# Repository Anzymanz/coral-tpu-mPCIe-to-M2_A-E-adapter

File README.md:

An M.2 A+E to mPCIe adapter for coral TPU

The capacitors most likely do not need to be populated

mPCIe Connector: [TE Connectivity 1775862-2](https://www.digikey.co.uk/en/products/detail/te-connectivity-amp-connectors/1775862-2/5430585)  
Standoffs: [Würth Elektronik 9774027151R](https://www.digikey.co.uk/en/products/detail/w%C3%BCrth-elektronik/9774027151R/5320625)  
  
**Make sure to disable ASPM to prevent the coral from sleeping and not being able to wake**  
Edit `/etc/default/grub`  
Example:  
`GRUB_CMDLINE_LINUX_DEFAULT="quiet intel_iommu=on pcie_aspm=off`

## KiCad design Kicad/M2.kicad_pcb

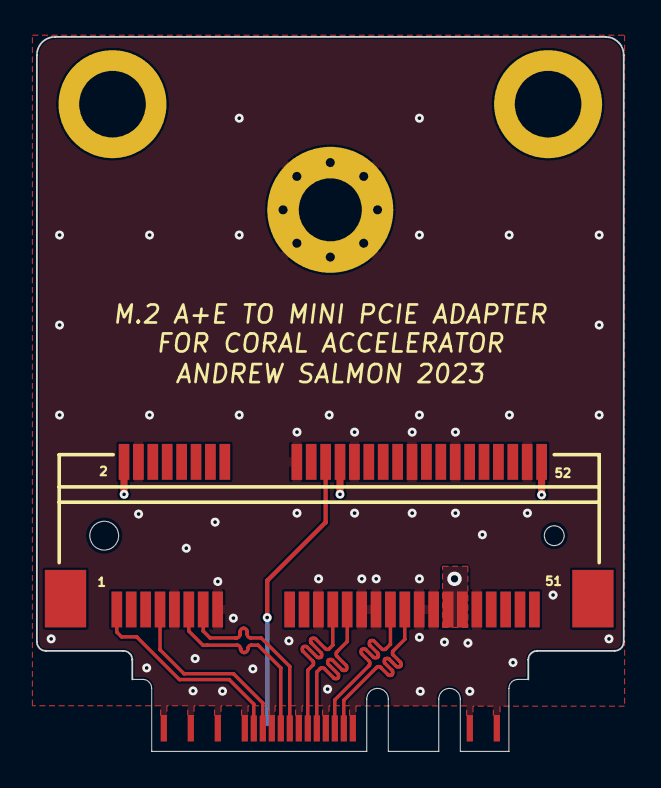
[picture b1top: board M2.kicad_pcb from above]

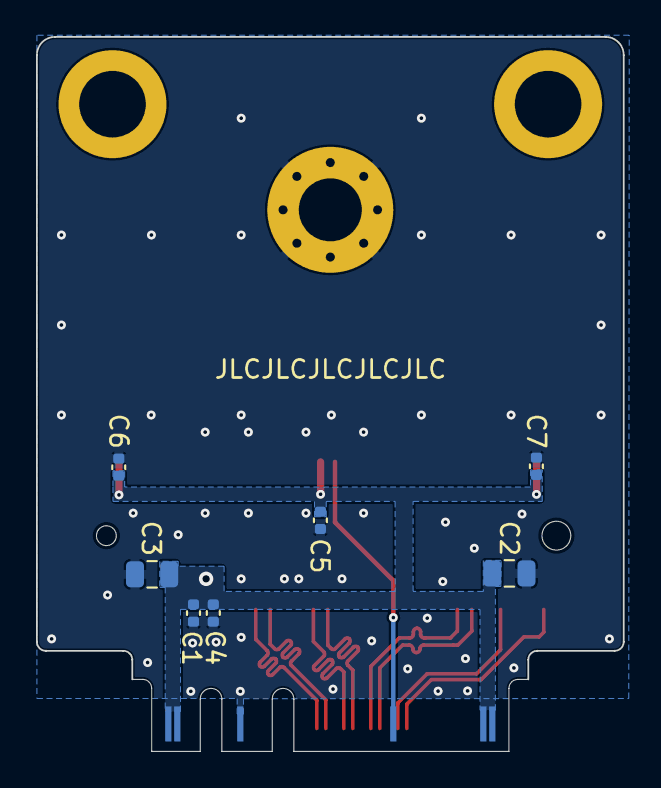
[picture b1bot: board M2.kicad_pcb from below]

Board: 2 copper layers, 32.6 x 39.7 mm, 12 parts (7 on the bottom side), 11 nets.

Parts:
C1, C4, C5, C6, C7: 0.1u; C_0402_1005Metric
C2, C3: 10u; C_0805_2012Metric
H1: MountingHole; MountingHole_3.5mm_Pad_Via
H2, H3: MountingHole; 9774027151R
J1: Bus_PCI_Express_Mini; TE_1775862-2
U1: M2_A+E; NGFF_A+E

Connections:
/3.3V: C1.2, C2.2, C3.2, C4.2, C5.1, C6.1, C7.1, J1.2 (+3V3AUX), J1.24 (+3V3AUX), J1.39 (+3V3AUX), J1.41 (+3V3AUX), J1.52 (+3V3AUX), U1.2 (3.3V), U1.4 (3.3V), U1.72 (3.3V), U1.74 (3.3V)
/PER_0+: J1.25 (PERp0), U1.41 (PERp0)
/PER_0-: J1.23 (PERn0), U1.43 (PERn0)
/PET_0+: J1.33 (PETp0), U1.35 (PETp0)
/PET_0-: J1.31 (PETn0), U1.37 (PETn0)
/REFCLK+: J1.13 (REFCLK+), U1.47 (REFCLKp0)
/REFCLK-: J1.11 (REFCLK-), U1.49 (REFCLKn0)
/~CLKREQ: J1.7 (~CLKREQ), U1.53 (~CLKREQ0)
/~PERST: J1.22 (~PERST), U1.52 (~PERST0)
/~PEWAKE: J1.1 (~WAKE), U1.55 (~PEWAKE0)
GND: C1.1, C2.1, C3.1, C4.1, C5.2, C6.2, C7.2, H1.1, J1.4 (GND), J1.9 (GND), J1.15 (GND), J1.18 (GND), J1.21 (GND), J1.26 (GND), J1.27 (GND), J1.29 (GND), J1.34 (GND), J1.35 (GND), J1.37 (GND), J1.40 (GND), J1.43 (GND), J1.50 (GND), U1.1 (GND), U1.7 (GND), U1.18 (GND), U1.33 (GND), U1.39 (GND), U1.45 (GND), U1.51 (GND), U1.57 (GND), U1.63 (GND), U1.69 (GND), U1.75 (GND)

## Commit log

2023-02-04 Rename M2.kicad_pcb to kICAD/M2.kicad_pcb
2023-02-04 Rename kICAD/M2.kicad_pcb to Kicad/M2.kicad_pcb
2023-02-04 Rename M2.kicad_prl to Kicad/M2.kicad_prl
2023-02-04 Rename M2.kicad_pro to Kicad/M2.kicad_pro
2023-02-04 Rename M2.kicad_sch to Kicad/M2.kicad_sch
2023-02-04 Create i
2023-07-10 Create LICENSE
